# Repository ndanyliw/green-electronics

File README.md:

# Green Electronics Repo
Libraries and code base for Stanford Green Electronics (EE155). This repository contains resources required for completing the labs and final project.

## Setup

Before you can program the STM32 development boards, you will need to set up the necessary toolchain on your machine. The toolchain has been tested on Ubuntu 14.04 which we suggest using for this toolchain. Other distributions/OSs will be left for you to setup and debug if you wish :).

Included in this repo is a script to install the necessary dependancies and setup the tools necessary for embedded ARM development. To run the script simply type `./setup.sh`. Note that you will be promped for your root password several times as it moves through the installation.

The tools will be installed in `~/ee155_tools` and you must run `source ~/ee155_tools/env.sh` before using the toolchain to put it on your path.

## Using the template

The template is adapted from mblythe86's F3 template: https://github.com/mblythe86/stm32f3-discovery-basic-template. This template provides an easy starter project that can take advantage of the standard libraries provided by STMicroelectronics and interface with a simple Makefile.

When starting a new project simply copy the template into a new folder with the following command `cp -r project-template my-new-project-name` and begin development. Depending on where you copy the project folder, you may need to modify the `EE155_LIB` parameter in the `Makefile`. Make sure that it points to the `libraries` folder.

The included Makefile will automatically detect all C source code in the `inc` and `src` directories. To compile the project run `make all`. Likewise to program the board, run `make program`. Additionally, the STM32F3 has the option to run GDB remotely on the board allowing you to interactively debug your code on the processor. Run `make debug` to program the board and launch GDB.

## Libraries

This repository includes a set of EE155 standard libraries used in this class. They are automatically linked against your code with the included Makefile. Under the `libraries` directory is also where you can install other custom libraries you find helpful.

Please take a look at the libraries to see what functionality is available to you.

## Datasheets

For convenience we have the most used datasheets when developing for the STM32F303 microprocessor. These are useful for figuring out pin mappings and registers especially when going past what the included libraries provide.

## Hardware

For reference the hardware designs used in this class are included.

## Labs

In the `labs` folder you will find starter code for the various labs.

## init_bitbucket

Included in the repository is an `init_bitbucket.sh` script. This file is included to automate the process of mapping the repository to a new, private repository hosted by bitbucket. Before running this script, you need to have created a bitbucket account. After execution, you will have initialized a new private repo and `git push` and `git pull` will be mapped there by default.

To pull the latest patches (which should be done at least once before starting a new lab) run `git pull upstream master`.

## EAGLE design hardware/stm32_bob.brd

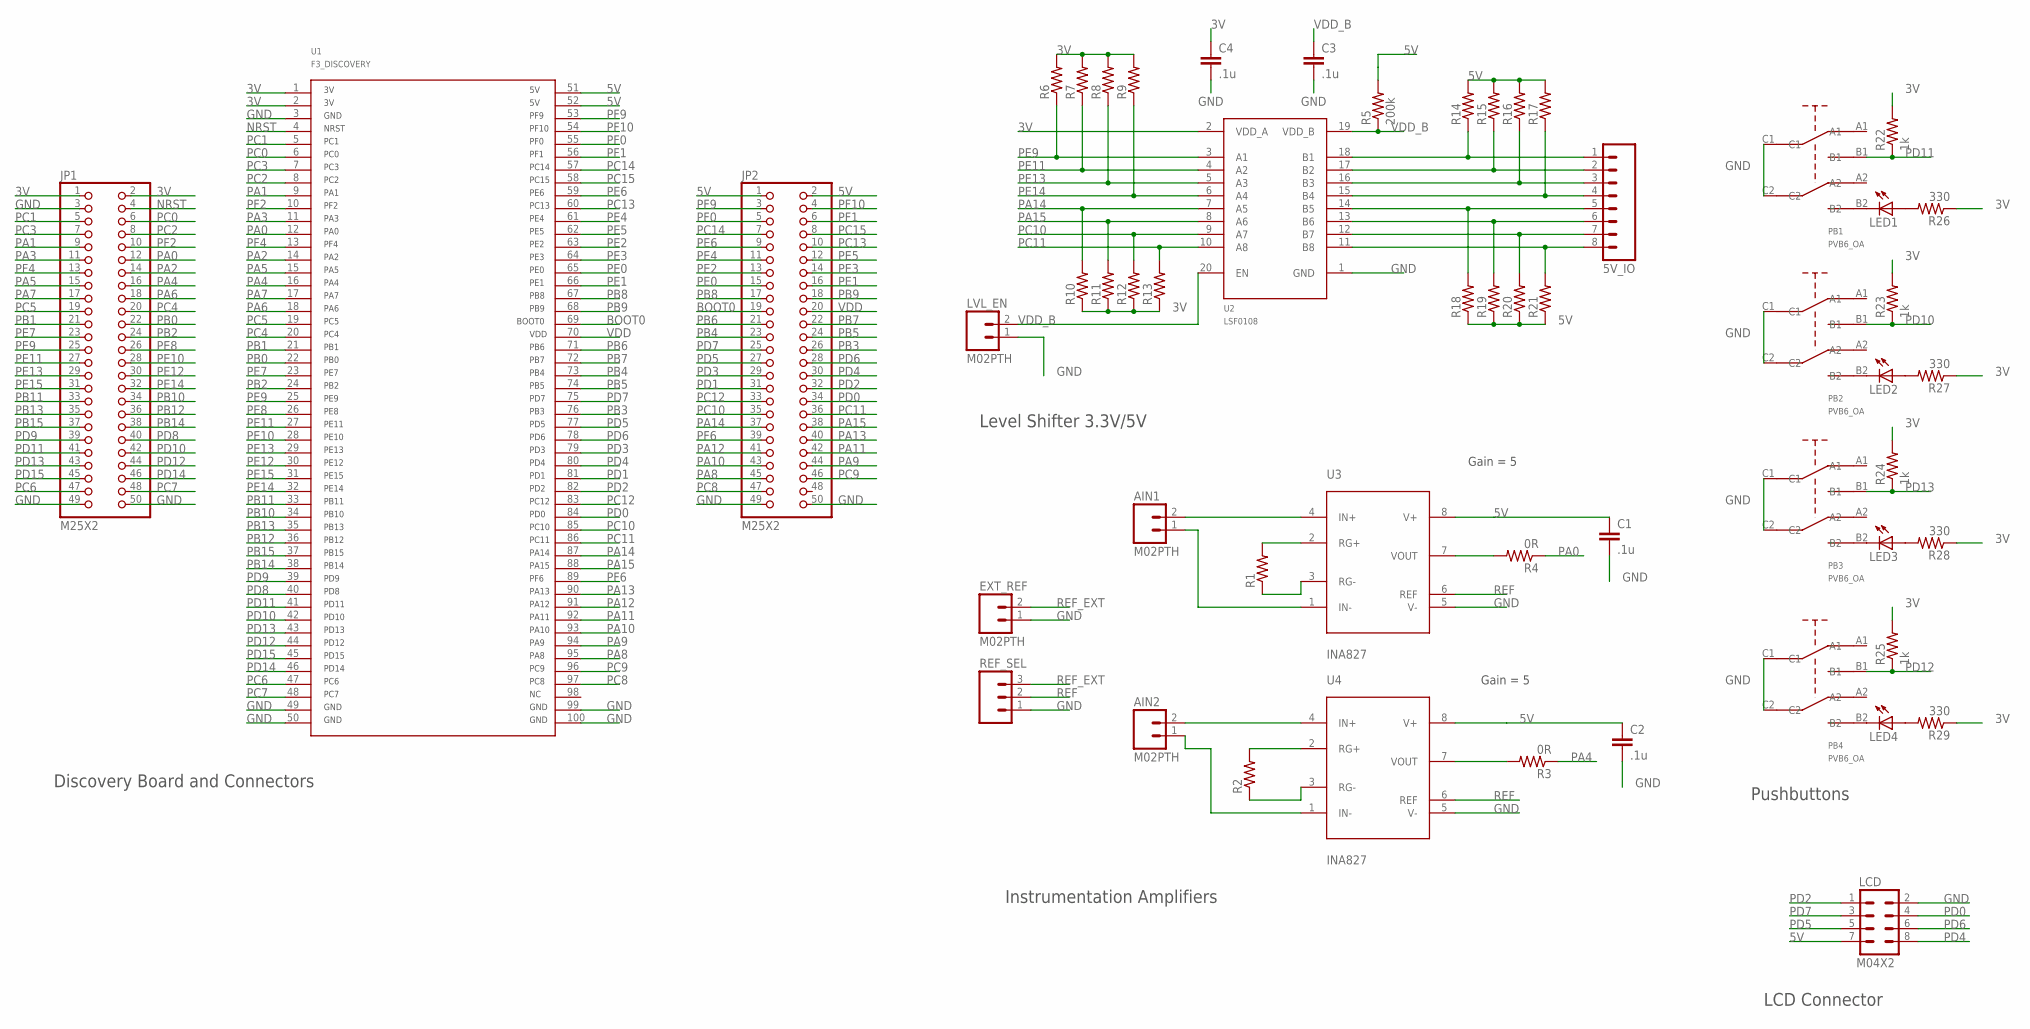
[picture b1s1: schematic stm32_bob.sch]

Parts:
5V_IO: M081X08; 1X08
AIN1, AIN2: M02PTH; 1X02
C1, C2, C3, C4: .1u; C0805
EXT_REF: M02PTH; 1X02
JP1, JP2: M25X2; 2X25
LCD: M04X2; 2X4
LED1, LED2, LED3, LED4: LED1206; LED-1206
LVL_EN: M02PTH; 1X02
PB1, PB2, PB3, PB4: PVB6_OA
R1, R2: R-US_R1206; R1206
R3, R4: 0R; R1206
R5: 200k; R0805
R6, R7, R8, R9, R10, R11, R12, R13, R14, R15, R16, R17, R18, R19, R20, R21: R-US_R0805; R0805
R22, R23, R24, R25: 1k; R0805
R26, R27, R28, R29: 330; R0805
REF_SEL: M03PTH; 1X03
U1: F3_DISCOVERY
U2: LSF0108
U3, U4: INA827; MSOP8

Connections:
3V: C4.1, JP1.1, JP1.2, R6.2, R7.2, R8.2, R9.2, R10.1, R11.1, R12.1, R13.1, R22.2, R23.2, R24.2, R25.2, R26.1, R27.1, R28.1, R29.1, U1.1, U1.2, U2.2 (VDD_A)
5V: C1.1, C2.1, JP2.1, JP2.2, LCD.7, R5.2, R14.2, R15.2, R16.2, R17.2, R18.1, R19.1, R20.1, R21.1, U1.51, U1.52, U3.8 (V+), U4.8 (V+)
BOOT0: JP2.19, U1.69
GND: C1.2, C2.2, C3.2, C4.2, EXT_REF.1, JP1.3, JP1.49, JP1.50, JP2.49, JP2.50, LCD.2, LVL_EN.1, PB1.C1, PB1.C2, PB2.C1, PB2.C2, PB3.C1, PB3.C2, PB4.C1, PB4.C2, REF_SEL.1, U1.3, U1.49, U1.50, U1.99, U1.100, U2.1 (GND), U3.5 (V-), U4.5 (V-)
unnamed: 5V_IO.1, R14.1, U2.18 (B1)
unnamed: 5V_IO.2, R15.1, U2.17 (B2)
unnamed: 5V_IO.3, R16.1, U2.16 (B3)
unnamed: 5V_IO.4, R17.1, U2.15 (B4)
unnamed: 5V_IO.5, R18.2, U2.14 (B5)
unnamed: 5V_IO.6, R19.2, U2.13 (B6)
unnamed: 5V_IO.7, R20.2, U2.12 (B7)
unnamed: 5V_IO.8, R21.2, U2.11 (B8)
unnamed: AIN1.1, U3.1 (IN-)
unnamed: AIN1.2, U3.4 (IN+)
unnamed: AIN2.2, U4.4 (IN+)
unnamed: AIN2.1, U4.1 (IN-)
unnamed: R1.2, U3.2 (RG+)
unnamed: R1.1, U3.3 (RG-)
unnamed: R2.2, U4.2 (RG+)
unnamed: R2.1, U4.3 (RG-)
unnamed: R4.2, U3.7 (VOUT)
unnamed: R3.2, U4.7 (VOUT)
unnamed: LED1.C, PB1.B2
unnamed: LED2.C, PB2.B2
unnamed: LED3.C, PB3.B2
unnamed: LED4.C, PB4.B2
unnamed: LED1.A, R26.2
unnamed: LED2.A, R27.2
unnamed: LED3.A, R28.2
unnamed: LED4.A, R29.2
NRST: JP1.4, U1.4
PA0: JP1.12, R4.1, U1.12
PA1: JP1.9, U1.9
PA2: JP1.14, U1.14
PA3: JP1.11, U1.11
PA4: JP1.16, R3.1, U1.16
PA5: JP1.15, U1.15
PA6: JP1.18, U1.18
PA7: JP1.17, U1.17
PA8: JP2.45, U1.95
PA9: JP2.44, U1.94
PA10: JP2.43, U1.93
PA11: JP2.42, U1.92
PA12: JP2.41, U1.91
PA13: JP2.40, U1.90
PA14: JP2.37, R10.2, U1.87, U2.7 (A5)
PA15: JP2.38, R11.2, U1.88, U2.8 (A6)
PB0: JP1.22, U1.22
PB1: JP1.21, U1.21
PB2: JP1.24, U1.24
PB3: JP2.26, U1.76
PB4: JP2.23, U1.73
PB5: JP2.24, U1.74
PB6: JP2.21, U1.71
PB7: JP2.22, U1.72
PB8: JP2.17, U1.67
PB9: JP2.18, U1.68
PB10: JP1.34, U1.34
PB11: JP1.33, U1.33
PB12: JP1.36, U1.36
PB13: JP1.35, U1.35
PB14: JP1.38, U1.38
PB15: JP1.37, U1.37
PC0: JP1.6, U1.6
PC1: JP1.5, U1.5
PC2: JP1.8, U1.8
PC3: JP1.7, U1.7
PC4: JP1.20, U1.20
PC5: JP1.19, U1.19
PC6: JP1.47, U1.47
PC7: JP1.48, U1.48
PC8: JP2.47, U1.97
PC9: JP2.46, U1.96
PC10: JP2.35, R12.2, U1.85, U2.9 (A7)
PC11: JP2.36, R13.2, U1.86, U2.10 (A8)
PC12: JP2.33, U1.83
PC13: JP2.10, U1.60
PC14: JP2.7, U1.57
PC15: JP2.8, U1.58
PD0: JP2.34, LCD.4, U1.84
PD1: JP2.31, U1.81
PD2: JP2.32, LCD.1, U1.82
PD3: JP2.29, U1.79
PD4: JP2.30, LCD.8, U1.80
PD5: JP2.27, LCD.5, U1.77
PD6: JP2.28, LCD.6, U1.78
PD7: JP2.25, LCD.3, U1.75
PD8: JP1.40, U1.40
PD9: JP1.39, U1.39
PD10: JP1.42, PB2.B1, R23.1, U1.42
PD11: JP1.41, PB1.B1, R22.1, U1.41
PD12: JP1.44, PB4.B1, R25.1, U1.44
PD13: JP1.43, PB3.B1, R24.1, U1.43
PD14: JP1.46, U1.46
PD15: JP1.45, U1.45
PE0: JP2.15, U1.65
PE1: JP2.16, U1.66
PE2: JP2.13, U1.63
PE3: JP2.14, U1.64
PE4: JP2.11, U1.61
PE5: JP2.12, U1.62
PE6: JP2.9, U1.59
PE7: JP1.23, U1.23
PE8: JP1.26, U1.26
PE9: JP1.25, R6.1, U1.25, U2.3 (A1)
PE10: JP1.28, U1.28
PE11: JP1.27, R7.1, U1.27, U2.4 (A2)
PE12: JP1.30, U1.30
PE13: JP1.29, R8.1, U1.29, U2.5 (A3)
PE14: JP1.32, R9.1, U1.32, U2.6 (A4)
PE15: JP1.31, U1.31
PF0: JP2.5, U1.55
PF1: JP2.6, U1.56
PF2: JP1.10, U1.10
PF4: JP1.13, U1.13
PF6: JP2.39, U1.89
PF9: JP2.3, U1.53
PF10: JP2.4, U1.54
REF: REF_SEL.2, U3.6 (REF), U4.6 (REF)
REF_EXT: EXT_REF.2, REF_SEL.3
VDD: JP2.20, U1.70
VDD_B: C3.1, LVL_EN.2, R5.1, U2.19 (VDD_B), U2.20 (EN)

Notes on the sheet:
Discovery Board and Connectors
Level Shifter 3.3V/5V
Instrumentation Amplifiers
LCD Connector
Pushbuttons
Gain = 5

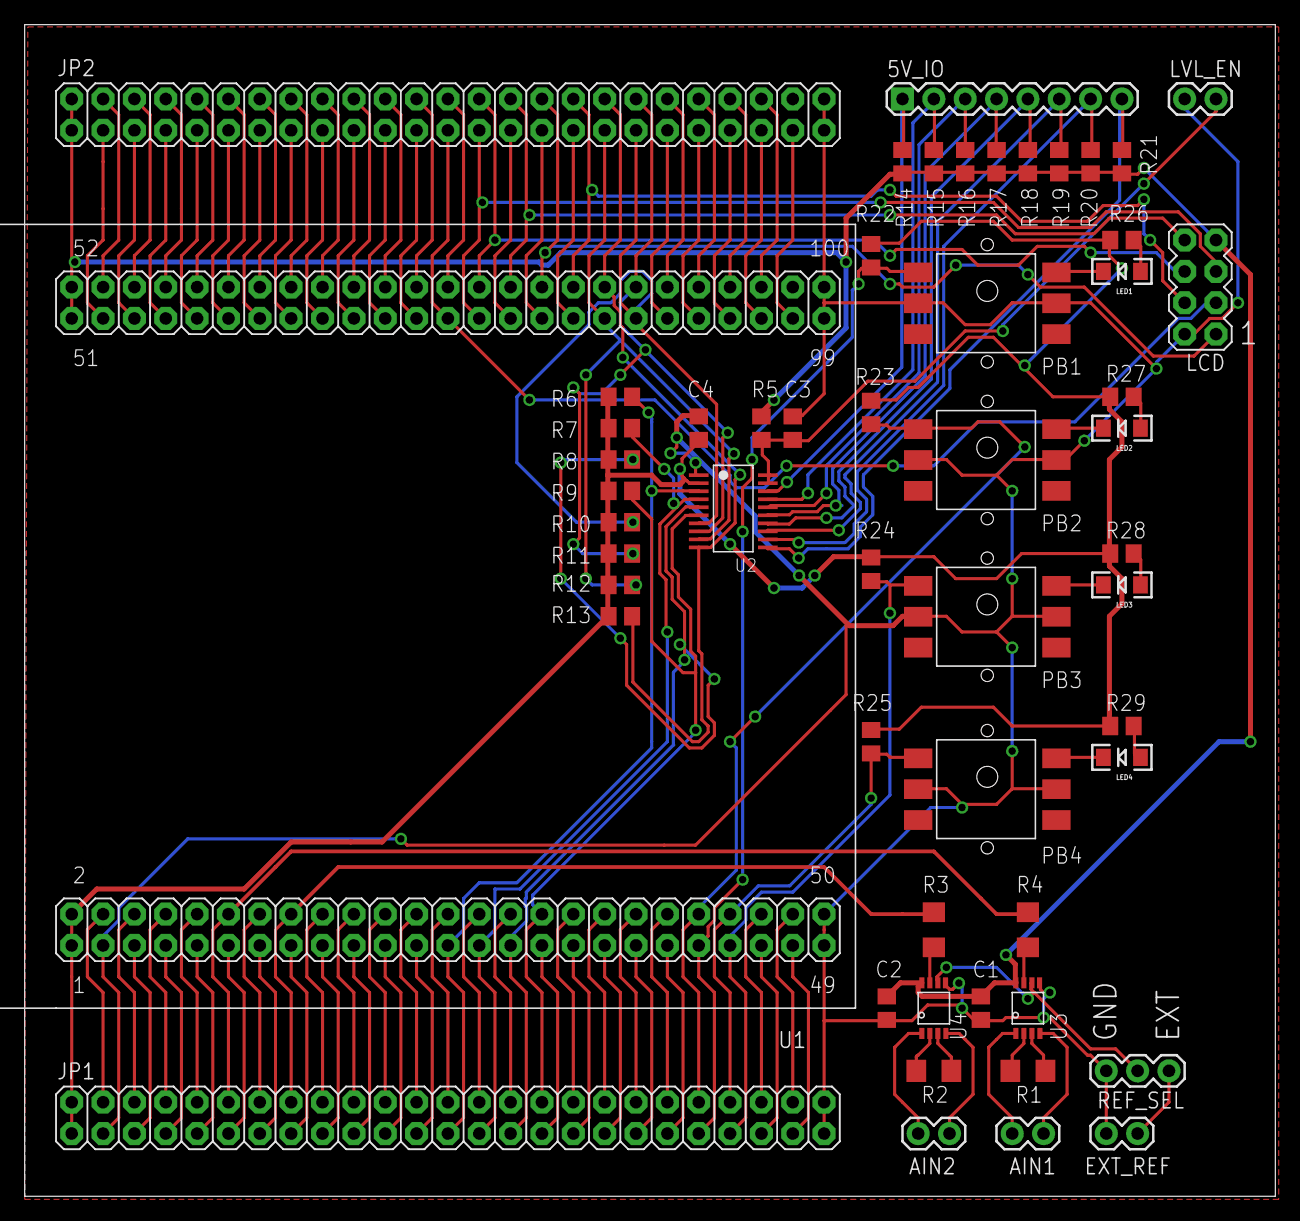
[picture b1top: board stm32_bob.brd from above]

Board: 2 copper layers, 101.3 x 94.9 mm, 54 parts (0 on the bottom side), 122 nets.

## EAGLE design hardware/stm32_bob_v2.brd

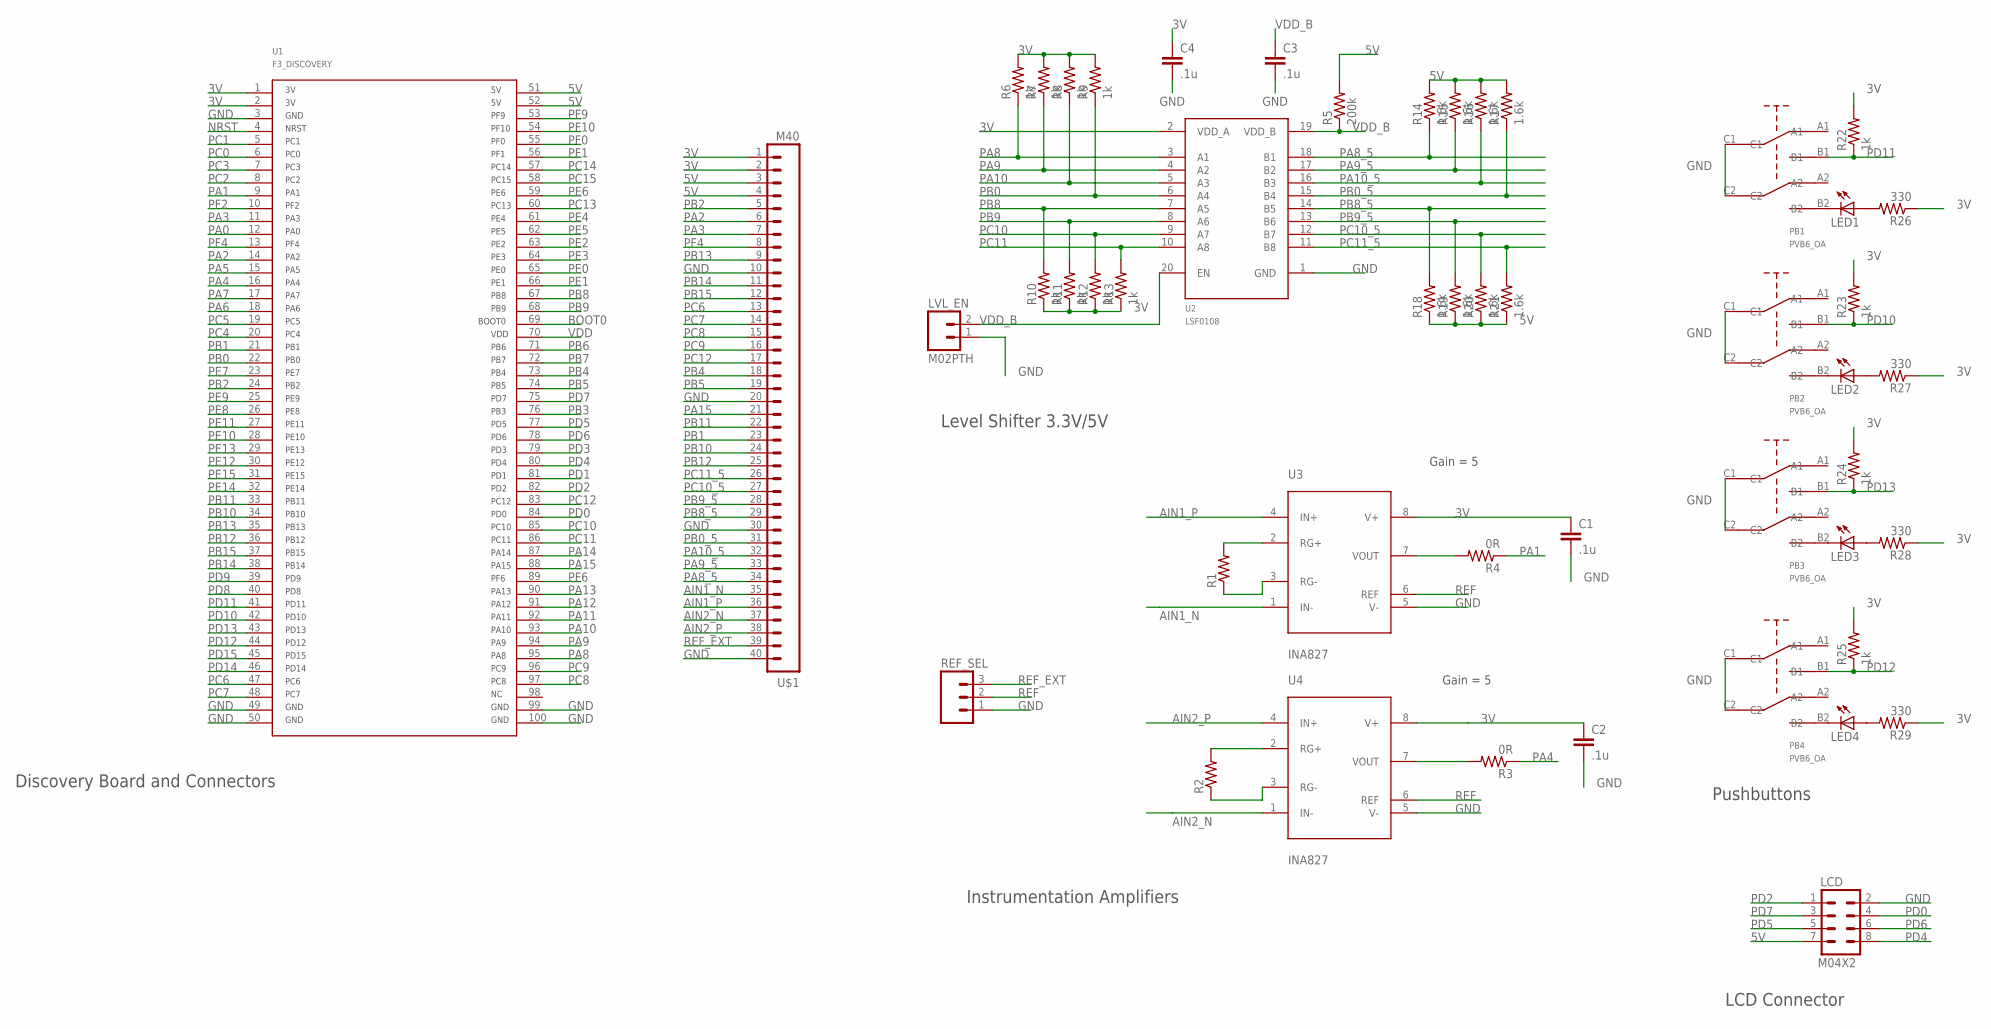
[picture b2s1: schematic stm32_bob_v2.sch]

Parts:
C1, C2, C3, C4: .1u; C0805
LCD: M04X2; 2X4
LED1, LED2, LED3, LED4: LED1206; LED-1206
LVL_EN: M02PTH; 1X02
PB1, PB2, PB3, PB4: PVB6_OA
R1, R2: R-US_R1206; R1206
R3, R4: 0R; R1206
R5: 200k; R0805
R6, R7, R8, R9, R10, R11, R12, R13, R22, R23, R24, R25: 1k; R0805
R14, R15, R16, R17, R18, R19, R20, R21: 1.6k; R0805
R26, R27, R28, R29: 330; R0805
REF_SEL: M03PTH; 1X03
U1: F3_DISCOVERY
U2: LSF0108
U3, U4: INA827; MSOP8
U$1: M40; 1X40

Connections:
3V: C1.1, C2.1, C4.1, R6.2, R7.2, R8.2, R9.2, R10.1, R11.1, R12.1, R13.1, R22.2, R23.2, R24.2, R25.2, R26.1, R27.1, R28.1, R29.1, U1.1, U1.2, U2.2 (VDD_A), U3.8 (V+), U4.8 (V+), U$1.1, U$1.2
5V: LCD.7, R5.2, R14.2, R15.2, R16.2, R17.2, R18.1, R19.1, R20.1, R21.1, U1.51, U1.52, U$1.3, U$1.4
AIN1_N: U3.1 (IN-), U$1.35
AIN1_P: U3.4 (IN+), U$1.36
AIN2_N: U4.1 (IN-), U$1.37
AIN2_P: U4.4 (IN+), U$1.38
BOOT0: U1.69
GND: C1.2, C2.2, C3.2, C4.2, LCD.2, LVL_EN.1, PB1.C1, PB1.C2, PB2.C1, PB2.C2, PB3.C1, PB3.C2, PB4.C1, PB4.C2, REF_SEL.1, U1.3, U1.49, U1.50, U1.99, U1.100, U2.1 (GND), U3.5 (V-), U4.5 (V-), U$1.10, U$1.20, U$1.30, U$1.40
unnamed: R1.2, U3.2 (RG+)
unnamed: R1.1, U3.3 (RG-)
unnamed: R2.2, U4.2 (RG+)
unnamed: R2.1, U4.3 (RG-)
unnamed: R4.2, U3.7 (VOUT)
unnamed: R3.2, U4.7 (VOUT)
unnamed: LED1.C, PB1.B2
unnamed: LED2.C, PB2.B2
unnamed: LED3.C, PB3.B2
unnamed: LED4.C, PB4.B2
unnamed: LED1.A, R26.2
unnamed: LED2.A, R27.2
unnamed: LED3.A, R28.2
unnamed: LED4.A, R29.2
NRST: U1.4
PA0: U1.12
PA1: R4.1, U1.9
PA2: U1.14, U$1.6
PA3: U1.11, U$1.7
PA4: R3.1, U1.16
PA5: U1.15
PA6: U1.18
PA7: U1.17
PA8: R6.1, U1.95, U2.3 (A1)
PA8_5: R14.1, U2.18 (B1), U$1.34
PA9: R7.1, U1.94, U2.4 (A2)
PA9_5: R15.1, U2.17 (B2), U$1.33
PA10: R8.1, U1.93, U2.5 (A3)
PA10_5: R16.1, U2.16 (B3), U$1.32
PA11: U1.92
PA12: U1.91
PA13: U1.90
PA14: U1.87
PA15: U1.88, U$1.21
PB0: R9.1, U1.22, U2.6 (A4)
PB0_5: R17.1, U2.15 (B4), U$1.31
PB1: U1.21, U$1.23
PB2: U1.24, U$1.5
PB3: U1.76
PB4: U1.73, U$1.18
PB5: U1.74, U$1.19
PB6: U1.71
PB7: U1.72
PB8: R10.2, U1.67, U2.7 (A5)
PB8_5: R18.2, U2.14 (B5), U$1.29
PB9: R11.2, U1.68, U2.8 (A6)
PB9_5: R19.2, U2.13 (B6), U$1.28
PB10: U1.34, U$1.24
PB11: U1.33, U$1.22
PB12: U1.36, U$1.25
PB13: U1.35, U$1.9
PB14: U1.38, U$1.11
PB15: U1.37, U$1.12
PC0: U1.6
PC1: U1.5
PC2: U1.8
PC3: U1.7
PC4: U1.20
PC5: U1.19
PC6: U1.47, U$1.13
PC7: U1.48, U$1.14
PC8: U1.97, U$1.15
PC9: U1.96, U$1.16
PC10: R12.2, U1.85, U2.9 (A7)
PC10_5: R20.2, U2.12 (B7), U$1.27
PC11: R13.2, U1.86, U2.10 (A8)
PC11_5: R21.2, U2.11 (B8), U$1.26
PC12: U1.83, U$1.17
PC13: U1.60
PC14: U1.57
PC15: U1.58
PD0: LCD.4, U1.84
PD1: U1.81
PD2: LCD.1, U1.82
PD3: U1.79
PD4: LCD.8, U1.80
PD5: LCD.5, U1.77
PD6: LCD.6, U1.78
PD7: LCD.3, U1.75
PD8: U1.40
PD9: U1.39
PD10: PB2.B1, R23.1, U1.42
PD11: PB1.B1, R22.1, U1.41
PD12: PB4.B1, R25.1, U1.44
PD13: PB3.B1, R24.1, U1.43
PD14: U1.46
PD15: U1.45
PE0: U1.65
PE1: U1.66
PE2: U1.63
PE3: U1.64
PE4: U1.61
PE5: U1.62
PE6: U1.59
PE7: U1.23
PE8: U1.26
PE9: U1.25
PE10: U1.28
PE11: U1.27
PE12: U1.30
PE13: U1.29
PE14: U1.32
PE15: U1.31
PF0: U1.55
PF1: U1.56
PF2: U1.10
PF4: U1.13, U$1.8
PF6: U1.89
PF9: U1.53
PF10: U1.54
REF: REF_SEL.2, U3.6 (REF), U4.6 (REF)
REF_EXT: REF_SEL.3, U$1.39
VDD: U1.70
VDD_B: C3.1, LVL_EN.2, R5.1, U2.19 (VDD_B), U2.20 (EN)

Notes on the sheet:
Discovery Board and Connectors
Level Shifter 3.3V/5V
Instrumentation Amplifiers
LCD Connector
Pushbuttons
Gain = 5

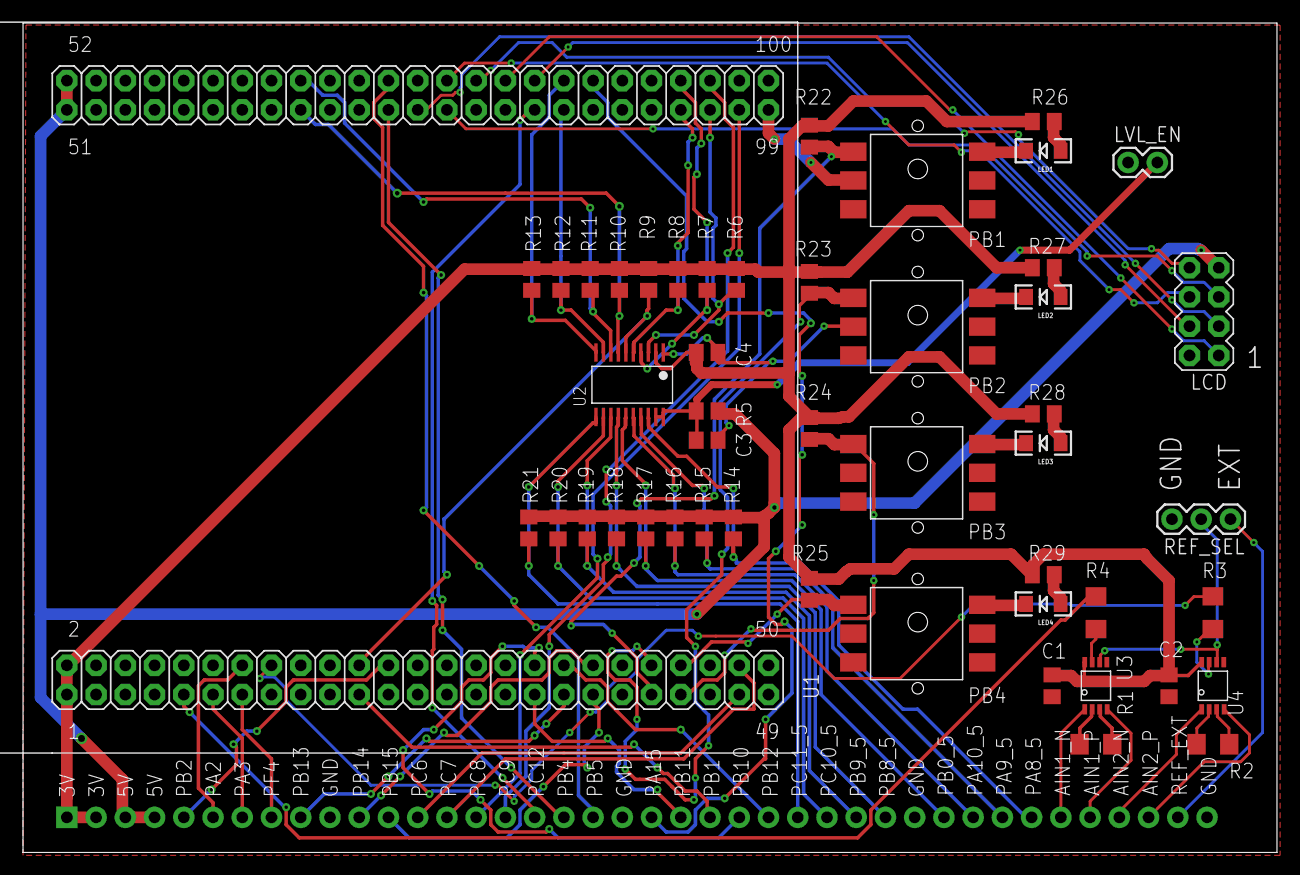
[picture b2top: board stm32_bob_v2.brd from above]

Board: 2 copper layers, 108.9 x 72.1 mm, 49 parts (0 on the bottom side), 71 nets.

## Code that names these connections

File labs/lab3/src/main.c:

/**
 * @file  main.c
 * @brief Hello World demo for the Green Electronics libraries.
 * 
 * @details Demos the basic functionality of the Green Electronics
 * libraries.
 * 
 * @author Ned Danyliw
 * @date  09.2016
 */
#include "ge_libs.h"
#include <stdio.h>

__IO bool led_state;

bool led_speed;
timer_id_t led_timer;

// keep track of what state the board is in
uint8_t ui_state;

#define NUM_STATES 4
// enumerate states
enum UI_STATE {
  LED_DEMO, PWM_DEMO, ADC_DEMO, USART_DEMO
};

// ADC variables
#define NUM_ADC 4
__IO uint16_t val[NUM_ADC];
ADC_CHAN_Type chan_to_conv[NUM_ADC] = {
  GE_ADC1_2, GE_ADC1_3, GE_ADC1_4, GE_ADC2_1
};
int num_refresh;

void setup_led_gpio() {
  //Initialize LED pins and set as outputs
  gpio_setup_pin(DISC_LD3, GPIO_OUTPUT, false, false);
  gpio_setup_pin(DISC_LD4, GPIO_OUTPUT, false, false);
  gpio_setup_pin(DISC_LD5, GPIO_OUTPUT, false, false);
  gpio_setup_pin(DISC_LD6, GPIO_OUTPUT, false, false);
  gpio_setup_pin(DISC_LD7, GPIO_OUTPUT, false, false);
  gpio_setup_pin(DISC_LD8, GPIO_OUTPUT, false, false);
  gpio_setup_pin(DISC_LD9, GPIO_OUTPUT, false, false);
  gpio_setup_pin(DISC_LD10, GPIO_OUTPUT, false, false);
}

void led_off() {
  gpio_write_pin(DISC_LD3, GPIO_LOW);
  gpio_write_pin(DISC_LD4, GPIO_LOW);
  gpio_write_pin(DISC_LD5, GPIO_LOW);
  gpio_write_pin(DISC_LD6, GPIO_LOW);
  gpio_write_pin(DISC_LD7, GPIO_LOW);
  gpio_write_pin(DISC_LD8, GPIO_LOW);
  gpio_write_pin(DISC_LD9, GPIO_LOW);
  gpio_write_pin(DISC_LD10, GPIO_LOW);
}

void led_on() {
  gpio_write_pin(DISC_LD3, GPIO_HIGH);
  gpio_write_pin(DISC_LD4, GPIO_HIGH);
  gpio_write_pin(DISC_LD5, GPIO_HIGH);
  gpio_write_pin(DISC_LD6, GPIO_HIGH);
  gpio_write_pin(DISC_LD7, GPIO_HIGH);
  gpio_write_pin(DISC_LD8, GPIO_HIGH);
  gpio_write_pin(DISC_LD9, GPIO_HIGH);
  gpio_write_pin(DISC_LD10, GPIO_HIGH);
}

// method to toggle LEDs
void toggle_led() {
  if (led_state) {
    led_off();
    led_state = false;
  } else {
    led_on();
    led_state = true;
  }
}

// handle initilization code for changing states
void change_state() {
  switch (ui_state) {
    case LED_DEMO:
      setup_led_gpio();
      led_timer = timer_register(500, &toggle_led, GE_PERIODIC);
      timer_start(led_timer);
      lcd_clear();
      lcd_goto(0, 0);
      lcd_puts("LED Demo");

      printf("LED Demo\n");
      break;
    case PWM_DEMO:
      // enable pwm pins
      pwm_set_pin(PE9);
      pwm_set_pin(PE11);
      pwm_set_pin(PE13);
      pwm_set_pin(PE14);

      lcd_clear();
      lcd_goto(0, 0);
      lcd_puts("PWM Demo");

      printf("PWM Demo\n");
      break;
    case ADC_DEMO:
      lcd_clear();
      lcd_goto(0, 0);
      lcd_puts("ADC Demo");

      printf("ADC Demo\n");
      break;
    case USART_DEMO:
      lcd_clear();
      lcd_goto(0, 0);
      lcd_puts("USART Demo");
      lcd_goto(0, 1);

      printf("USART Demo. Echo user input.\n");
      break;
    default:
      break;
  }
}

// ADC callback
void my_adc_callback(uint16_t *buf) {
  for (int k = 0; k < NUM_ADC; k++) {
    val[k] = buf[k];
  }
}


/**
  * @brief  Main program.
  * @param  None 
  * @retval None
  */
int main(void)
{  

  NVIC_PriorityGroupConfig(NVIC_PriorityGroup_2);
  // Initialize library
  ge_init();

  // Initialize LEDs
  setup_led_gpio();
  led_state = false;
  led_speed = false;

  // Initialize the USER button as an input
  gpio_setup_pin(GE_PBTN2, GPIO_INPUT, false, false);

  // Initialize PBTN1
  gpio_setup_pin(GE_PBTN1, GPIO_INPUT, false, false);

  // Print to serial port
  printf("Hello, World!\n");

  // Print Hello World
  lcd_clear();
  lcd_goto(0, 0);
  lcd_puts("Hello, World!");

  // Setup timer library
  // Set minimum timestep to 1ms (number of counts referecned to 
  // a 72MHz clock)
  timer_set_timestep(72000);
  // register callback for toggling LEDs every 500ms
  led_timer = timer_register(500, &toggle_led, GE_PERIODIC);
  timer_start(led_timer);

  // set mode to the LED demo
  ui_state = LED_DEMO;

  // set pwm level for PWM demo
  float pwm_level = 0.0;

  // setup PWM library
  pwm_freq(10000.0);

  // setup ADC
  // set sampling rate to 10kHz
  adc_set_fs(10000);
  // register ADC callback
  adc_callback(&my_adc_callback);
  // enable ADC channels
  adc_enable_channels(chan_to_conv, NUM_ADC);
  adc_initialize_channels();
  adc_start();

  // keep track of how many times the UI has looped
  num_refresh = 0;


  /* Infinite loop */
  /**
   * Handles the user interface state machine
   */
  while (1) {   
    switch (ui_state) {
      /**
       * User can toggle the flashing speed of the Discovery board
       * LEDs. This demos how the timer library can be used.
       */
      case LED_DEMO:
        //check if button depressed
        if (!gpio_read_pin(GE_PBTN2)) {
          if (led_speed) {
            timer_set_period(led_timer, 500);
            led_speed = false;
          } else {
            timer_set_period(led_timer, 100);
            led_speed = true;
          }

          // wait for button to be released
          while (!gpio_read_pin(GE_PBTN2));
        }
        break;

      case PWM_DEMO:
        pwm_level = pwm_level + .05;

        if (pwm_level > 1.0) pwm_level = 0.0;

        pwm_set(PWM_CHAN1, pwm_level);
        pwm_set(PWM_CHAN2, pwm_level);
        pwm_set(PWM_CHAN3, pwm_level);
        pwm_set(PWM_CHAN4, pwm_level);
        break;

      case ADC_DEMO:
        // print results every 10 refreshes
        num_refresh++;
        if (num_refresh >= 10) {
          num_refresh = 0;
          printf("%u\t%u\t%u\t%u\n", val[0], val[1], val[2], val[3]);
          // printf("%u\t%u\n", val[0], val[1]);
        }
        break;

      case USART_DEMO: ;
        if (ge_uart_available()) {
          uint8_t c = ge_uart_get();
          printf("%c\n", c);
          lcd_putc(c);
        }
        break;

      default:
        break;
    }

    // check whether to change state
    if (!gpio_read_pin(GE_PBTN1)) {
      // stop LED timer if necessary
      if (ui_state == LED_DEMO) timer_stop(led_timer);

      ui_state++;
      if (ui_state >= NUM_STATES) ui_state = LED_DEMO;

      change_state();

      // wait for button to be released
      while (!gpio_read_pin(GE_PBTN1));
    }

    delay_ms(50);
  }
}



#ifdef  USE_FULL_ASSERT

/**
  * @brief  Reports the name of the source file and the source line number
  *         where the assert_param error has occurred.
  * @param  file: pointer to the source file name
  * @param  line: assert_param error line source number
  * @retval None
  */
void assert_failed(uint8_t* file, uint32_t line)
{ 
  /* User can add his own implementation to report the file name and line number,
     ex: printf("Wrong parameters value: file %s on line %d\r\n", file, line) */

  /* Infinite loop */
  while (1)
  {
  }
}
#endif

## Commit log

2015-09-08 Added setup script for toolchain
2015-09-08 Added blank project template
2015-09-08 Added microcontroller datasheets
2015-09-08 Added libraries used last year.
2015-09-09 Added breakout board design files
2015-09-09 Added values for populated components
2015-09-09 oops forgot one
2015-09-10 Fully routed board
2015-09-10 Added wrapper libraries for LCD lib
2015-09-10 renamed library files to ge_library_name
2015-09-12 Added version 2 of board using 40 pin header
2015-09-13 added gitignore
2015-09-13 changed io to avoid pins used on development board
2015-09-13 Fixed path for OCD in Makefile
2015-09-14 added library README and first implementation of lcd library
2015-09-14 added new library files to be written
2015-09-18 Timer library written
2015-09-19 Cleaned up timer variable comments
2015-09-19 Added custom pin definitions
2015-09-20 GPIO library written and fixed bug in pin definitions
2015-09-20 added system library
2015-09-21 Various fixes to libraries
2015-09-21 Compile green electronics library as linked static library
2015-09-21 Added Lab1 hello world starter code
2015-09-21 renamed ge_print to ge_vcom
2015-09-21 Added usb libraries to green electronics library to setup for ge_vcom
2015-09-22 Preliminary implementation of VCOM port
2015-09-22 Got VCOM demo mostly working
2015-09-22 renamed timer functions to match library naming scheme
2015-09-22 fixed naming for ge_pwm to match library naming
2015-09-23 Uncommented LCD code
2015-09-23 more work on VCOM library
2015-09-23 Added init_bitbucket script
2015-09-24 fixed init bitbucket script
2015-09-24 more fixes to init_bitbucket
2015-09-24 fixed init_bitbucket script for lubuntu
2015-09-24 updated linker script and fixed warnings in timer library
2015-09-24 Updated repo README
2015-09-24 updated main in project-template to use libraries and removed SysTick. Fixed warning in linker script
2015-09-24 Removed timer code from lab1 hello world main. Fixed warning in linker script
2015-09-24 Added to repo README
2015-09-24 added stubs for newlib support
2015-09-25 more linker fixes
2015-09-25 fixed timer interrupt handler
2015-09-25 bug fix with timer period. need to see why this fixes it...
2015-09-25 fixed linker error for project-template
2015-09-27 added slides on stm32 ADCs
2015-09-28 Moved linker scripts to base directory
2015-09-28 added starter code for lab2
2015-09-28 starter code mostly written for lab 2
2015-09-28 added virtual eeprom library
2015-09-29 added configurable pins for pwm library
2015-09-29 added pwm_set_pin function to ge_pwm
2015-09-29 fixed frequency issue with PWM library
2015-09-30 added volatile tag for adc readings in starter code.
2015-10-01 fixed bug in ge_eeprom library
2015-10-08 more aggressive .gitignore
2015-10-18 Added preliminary implementation of input capture libraries
2015-10-18 input capture seems to work. need to test with function generator
2015-10-24 fixed frequency calculation bug in library
2015-10-24 Added starter code for lab 5
2015-11-13 Fixed timer bug and added ability to change period
2015-12-08 fixed issue with volatile chan variable in ADC library
2016-04-11 added some stuff to set up the DMA
2016-05-29 current state on fixing adc and adding uart
2016-05-29 changed gpio init input capture
2016-05-29 use open drain for ic pin
2016-05-31 added software interrupt based input capture code
2016-08-03 in the process of adding uart support to green electronics libraries
2016-08-22 uart working with printf. still having difficulty reading from uart
2016-08-24 still having issues with conversions. seems that interrupts aren't retriggered. probably adc not getting triggered by clocks. going to revert to only ADC1 and ADC2
2016-08-24 working with seperate ADCs. but having an issue when using multiple channels on the same ADC. seems to be overwriting value before system has a chance to read the conversion value
2016-08-24 dma working with 2 channels on same ADC. need to expand to multiple ADCs and arbitrary number of channels per adc
2016-08-24 dma now working with timer trigger
2016-09-04 ADC conversions with arbitrary channel order and DMA on ADC1 and ADC2
2016-09-04 registered interrupt for ADC2 DMA
2016-09-06 implemented new hello world program which uses all of the functionality of the stm32 board
2016-09-06 updated pin definitions for new breakout board
2016-09-08 Added UART script
2016-09-08 Updated project template to hello world demo
2016-09-11 deleted compiled files in lab2
2016-09-11 updated lab2 starter code
2016-09-11 Added definitions for ge breakout board v2. added init code for eeprom
2016-09-12 updated lab2 newline_stubs
2016-09-12 Added lab3 starter files.
2016-09-13 fixed startup error with DMA
2016-09-13 changed to ICP on breakout board - pb10
2016-09-14 implemented software interrupt driven input capture for pb10
2016-09-14 added initilization code for soft input capture library
2016-09-14 updated lab5 starter code
2016-09-16 added lab6 starter code
2016-09-20 Cleaned adc library
2016-09-21 Commented rest of ge libraries
2016-09-21 cleaned up lab starter code
2016-09-21 update project template main file
2016-09-26 Cleaned lab6 starter code
2016-09-26 removed compiled files from lab2
2016-10-04 fixed lab2 starter code
2016-10-04 fixed ADC DMA bug
2016-10-31 added max frequency method to ic_capture and median filter to lab5 starter code
2016-10-31 Cleaned up lab5 starter code
2016-11-01 added pulse filtering to IC library
2016-11-05 fixed path bug in makefile for lab6 starter code
2017-10-03 stlinkv2 config fix + Makefile changes for new STM boards using new revision
2017-10-03 updated script fix for stm board
2017-10-06 updated gdb_cmds to use correct stlink

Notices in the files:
parts and their libraries:
SparkFun-Connectors: Licensing: CC v3.0 Share-Alike You are welcome to use this library for commercial purposes.
